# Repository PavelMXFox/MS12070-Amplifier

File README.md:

# Audio Amplifier System Design
##  Overview
This project is a professional-grade audio amplifier system featuring dual MA12070P Class-D amplifier chips in a 2×BTL configuration. The design includes a complete power supply section, digital signal processing (DSP) core, and control interfaces.

## Key Features
* Dual Channel Bi-Amplifier: 2×BTL configuration with MA12070P chips
* Digital Control: Integrated DSP for advanced audio processing
* Power Supply: 24V input with comprehensive protection circuitry
* Interfaces: I2C control, ADC inputs, and digital audio inputs
* Protection: Overvoltage, reverse polarity, and thermal monitoring

## Hardware Components
* Main Amplifiers: MA12070P Class-D amplifiers
* DSP Core: ADAU1452 audio processor
* Power Management: ADM1032 for rail monitoring
* Control MCU: STM32 microcontroller
* Audio Interfaces: PCM1808 for digital audio input

## Block Diagram Overview
The system consists of the following main sections:
* Power Section: 24V input with protection and distribution
* Amplifier Section: Dual MA12070P channels with complete driver circuitry
* DSP Section: Audio processing core with memory
* Control Section: MCU and interface circuits
* Audio Section: Input conditioning and output drivers

## Documentation
* Schematics: Detailed schematics for all sections
* PCB Layout: Professional-grade layout with proper grounding and power distribution
* Bill of Materials: Complete list of components
* Assembly Guide: Step-by-step assembly instructions
## License
This project is released under the TAPR Open Hardware License. All files are provided "as is" without warranty. For more details, see the LICENSE.TXT file.

## Contributions
* Original Power Supply Section: Based on Open Hardware DSP Platform (github.com:ohdsp/DSP-ADAU1452.git) under TAPR OHL
* Main Design: Developed by Pavel Dmitriev
* Modifications: See CHANGES.TXT for detailed list of changes

## How to Use
* Review the schematics and documentation
* Verify component compatibility
* Follow assembly guidelines
* Program the DSP and MCU
* Perform system calibration

## Known Issues
None reported at this time

## Contact
For questions or contributions, please contact:
GitHub: https://github.com/PavelMXFox

## Version History
* Initial release: November 2026
* Based on design principles from Open Hardware DSP Platform (github.com:ohdsp/DSP-ADAU1452.git)

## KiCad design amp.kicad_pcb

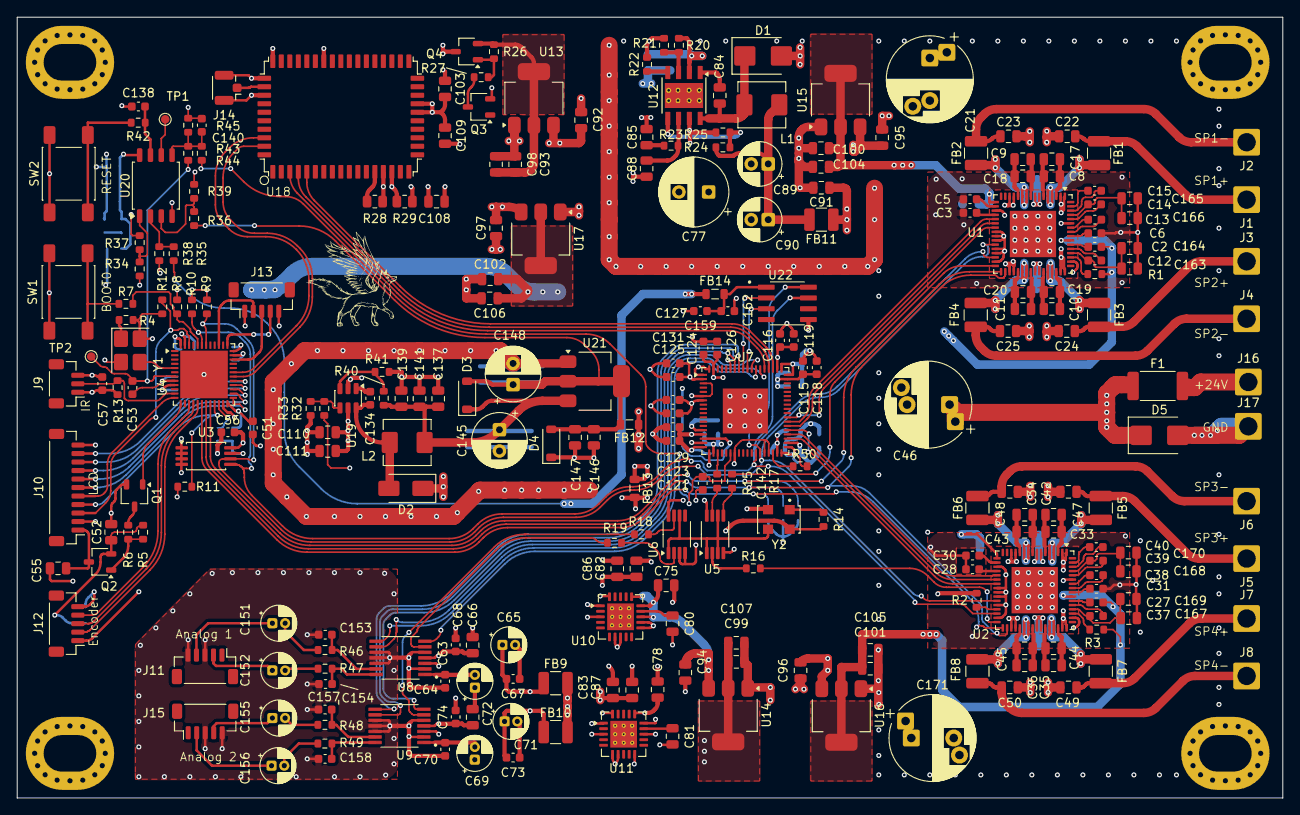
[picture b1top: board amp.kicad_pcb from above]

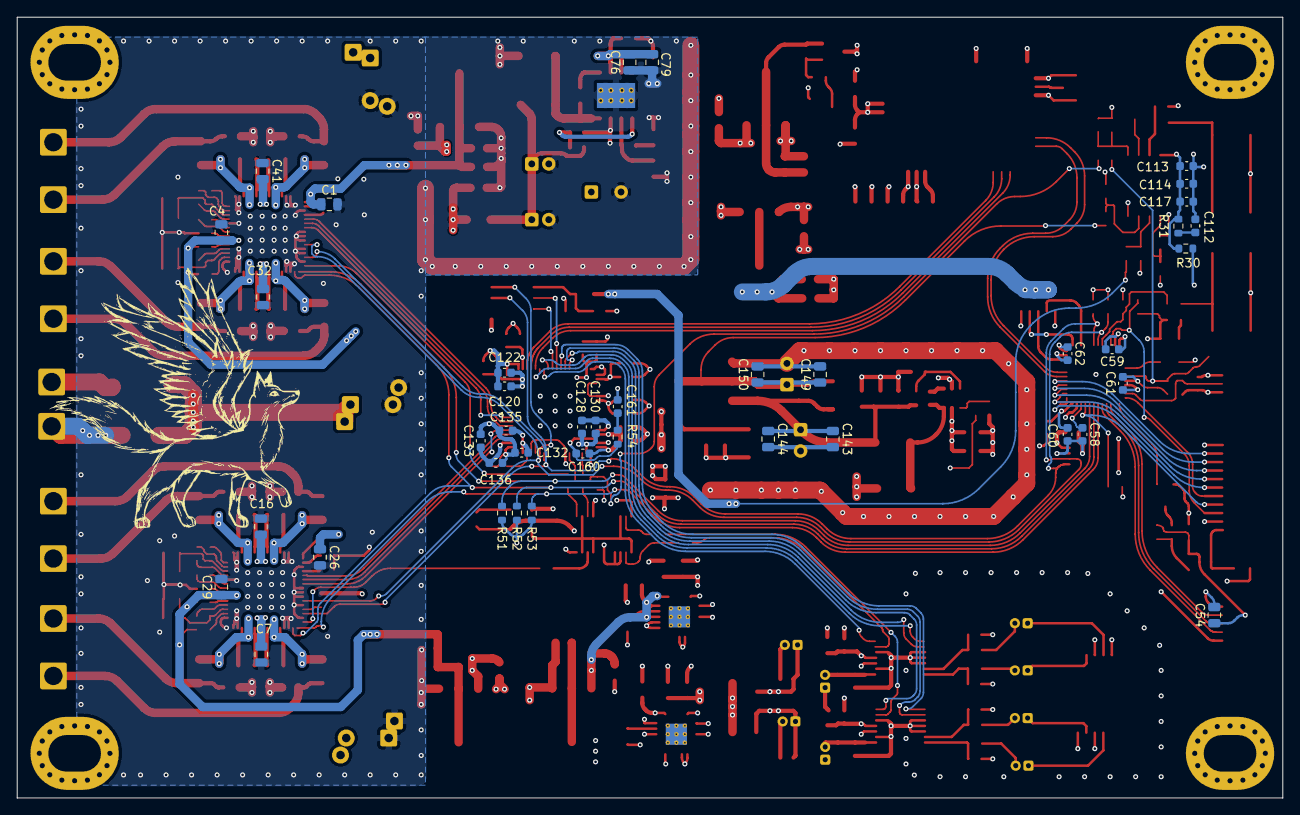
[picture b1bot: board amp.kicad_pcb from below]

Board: 4 copper layers, 148.8 x 91.8 mm, 296 parts (40 on the bottom side), 184 nets.

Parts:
C1, C4, C7, C16, C26, C29, C32, C41, C80, C81, C163, C165, C167, C168: 1uF; C_0805_2012Metric
C2, C3, C5, C6, C12, C13, C14, C27, C28, C30, C31, C37, C38, C39, C162: 1uF; C_0603_1608Metric
C8, C9, C10, C11, C17, C18, C19, C20, C33, C34, C35, C36, C42, C43, C44, C45, C52, C66, C72, C91, C92, C93, C94, C95, C96, C97, C99, C100, C101, C102, C108, C109: 10uF; C_0805_2012Metric
C15, C40, C64, C67, C68, C70, C73, C74, C159: 100nf; C_0603_1608Metric
C21, C46, C171: 470uF; CP_Radial_D10.0mm_P5.00mm_P7.50mm
C22, C23, C24, C25, C47, C48, C49, C50: 1nf; C_0805_2012Metric
C51, C53, C56, C59, C60, C61, C62, C114, C138, C140, C142: 100n; C_0603_1608Metric
C54, C55, C98, C103, C104, C105, C106, C107: 100nF; C_0805_2012Metric
C57, C118, C119, C122, C123, C126, C127, C130, C131, C135, C136: 100nF; C_0603_1608Metric
C58: 4.7uF; C_0603_1608Metric
C63, C65, C69, C71: 10uF; CP_Radial_D4.0mm_P1.50mm
C75, C78, C82, C83, C86, C87: 22uF; C_0805_2012Metric
C76, C79: 2.2uF; C_0805_2012Metric
C77: 100uF; CP_Radial_D8.0mm_P3.50mm
C84: 0.1uF; C_0805_2012Metric
C85: 6800pF; C_0805_2012Metric
C88: 39pF; C_0805_2012Metric
C89, C90: 47uF; CP_Radial_D5.0mm_P2.00mm
C110, C137, C139, C144, C147: 22u; C_0805_2012Metric
C111, C141, C143, C146, C149: 100n; C_0805_2012Metric
C112: 100p; C_0603_1608Metric
C113: 10u; C_0603_1608Metric
C115, C116, C120, C121, C124, C125, C128, C129, C132, C133: 10uF; C_0603_1608Metric
C117, C134: 10n; C_0603_1608Metric
C145, C148: 220u; CP_Radial_D6.3mm_P2.50mm
C150: 10u; C_0805_2012Metric
C151, C152, C155, C156: 2.2uF; CP_Radial_D4.0mm_P1.50mm
C153, C157: 1nF; C_0603_1608Metric
C154, C158: 1nf; C_0603_1608Metric
C160: 150pf; C_0603_1608Metric
C161: 5,6nF; C_0603_1608Metric
C164, C166, C169, C170: 100nf; C_0805_2012Metric
D1: B560C; D_SMB
D2: B240A; D_SMA
D3, D4: SS14L; D_SOD-123
D5: SMBJ24A; D_SMB
F1: 10A; Fuse_2512_6332Metric
FB1, FB2, FB3, FB4, FB5, FB6, FB7, FB8, FB11: FerriteBead; L_1210_3225Metric
FB9, FB10: L_1210_3225Metric
FB12, FB13, FB14: 600R@100MHz >1A; L_0805_2012Metric
J1, J5: SPK1P; SolderWire-1.5sqmm_1x01_D1.7mm_OD3mm
J2, J6: SPK1N; SolderWire-1.5sqmm_1x01_D1.7mm_OD3mm
J3, J7: SPK2P; SolderWire-1.5sqmm_1x01_D1.7mm_OD3mm
J4, J8: SPK2N; SolderWire-1.5sqmm_1x01_D1.7mm_OD3mm
J9: Conn_01x03; JST_SH_BM03B-SRSS-TB_1x03-1MP_P1.00mm_Vertical
J10: Conn_01x11; JST_SH_BM11B-SRSS-TB_1x11-1MP_P1.00mm_Vertical
J11, J15: Conn_01x05; JST_SH_BM05B-SRSS-TB_1x05-1MP_P1.00mm_Vertical
J12: Encoder; JST_SH_BM05B-SRSS-TB_1x05-1MP_P1.00mm_Vertical
J13: ST-Link; JST_SH_BM05B-SRSS-TB_1x05-1MP_P1.00mm_Vertical
J14: Conn_Coaxial; U.FL_Hirose_U.FL-R-SMT-1_Vertical
J16: 26V IN; SolderWire-1.5sqmm_1x01_D1.7mm_OD3mm
J17: GND; SolderWire-1.5sqmm_1x01_D1.7mm_OD3mm
L1, L2: 4.7uH; L_Sunlord_MWSA0518S
Q1, Q3: PDTC114ET; TSOT-23
Q2, Q4: IRLML2244; TSOT-23
R1, R2, R3: 1K; R_0603_1608Metric
R4, R8, R13, R50, R51, R52, R53: 10K; R_0603_1608Metric
R5, R26: 33K; R_0603_1608Metric
R6, R27: 330R; R_0603_1608Metric
R7, R46, R47, R48, R49: 100R; R_0603_1608Metric
R9, R10, R11, R12, R14: 4.7K; R_0603_1608Metric
R15, R16, R17, R18, R19: 33R; R_0603_1608Metric
R20: 523.0K; R_0603_1608Metric
R21: 84,5K; R_0603_1608Metric
R22: 45.3K; R_0603_1608Metric
R23: 13.0K; R_0603_1608Metric
R24: 66.5K; R_0603_1608Metric
R25: 10.2K; R_0603_1608Metric
R28: 1K; R_0805_2012Metric
R29: 100K; R_0805_2012Metric
R30: 1; R_0603_1608Metric
R31: 47; R_0603_1608Metric
R32: 16k; R_0603_1608Metric
R33: 10k; R_0603_1608Metric
R34: 0; R_0603_1608Metric
R35: 12k; R_0603_1608Metric
R36: 3k3; R_0603_1608Metric
R37: N/F; R_0603_1608Metric
R38: 3k; R_0603_1608Metric
R39: 3k6; R_0603_1608Metric
R40: 24k; R_0603_1608Metric
R41: 15k; R_0603_1608Metric
R42: 1k; R_0603_1608Metric
R43, R44: 100; R_0603_1608Metric
R45: 100k; R_0603_1608Metric
R54: 4,32K; R_0603_1608Metric
SW1: BOOT0; SW_Push_1P1T_NO_E-Switch_TL3301NxxxxxG
SW2: RESET; SW_Push_1P1T_NO_E-Switch_TL3301NxxxxxG
TP1, TP2: PIN; TestPoint_Pad_D1.0mm
U1, U2: MA12070P; QFN-64-1EP_9x9mm_P0.5mm_EP5.45x5.45mm
U3: 24LC256; TSSOP-8_4.4x3mm_P0.65mm
U4: STM32F411CEUx; QFN-48-1EP_7x7mm_P0.5mm_EP5.6x5.6mm
U5, U6: 74LVC3G34; Texas_S-PDSO-G8_3x3mm_P0.65mm
U7: ADAU1452; LFCSP-72-1EP_10x10mm_P0.5mm_EP5.3x5.3mm
U8, U9: PCM1808PWG4; SOP65P640X120-14N
U10, U11: TPS7A4701xRGW; Texas_RGW0020A_VQFN-20-1EP_5x5mm_P0.65mm_EP3.15x3.15mm_Ther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
U12: TPS54360DDA; TI_SO-PowerPAD-8_ThermalVias
U13, U14, U17: LDL1117-3.3; SOT-223-3_TabPin2
U15, U16: LDL1117-5; SOT-223-3_TabPin2
U18: QCC512X; QCC512X_Bluetooth_module
U19: ADP2301AUJZ; SOT-23-6
U20: ADM13307-5ARZ; SOIC-8_5.3x5.3mm_P1.27mm
U21: TLV1117LV12DCY; SOT-223-3_TabPin2
U22: ADM1032ARZ; SOIC127P600X175-8N
Y1: ASE-8MHz; Oscillator_SMD_Abracon_ASE-4Pin_3.2x2.5mm_HandSoldering
Y2: ASFLMB-12.288MHZ-LC-T; XTAL_ASFLMB-12.288MHZ-LC-T

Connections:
/Control plane/BOOT0: R7.2, R8.1, U4.44 (BOOT0)
/Control plane/CLK_8MHZ: U4.5 (PH0), Y1.3 (OUT)
/Control plane/SWCLK: J13.4, U4.37 (PA14)
/Control plane/SWDIO: J13.3, U4.34 (PA13)
/Control plane/SWO: J13.2, U4.39 (PB3)
/Power 2/2V1: C137.1, C139.1, C141.1, C143.1, C144.1, C145.1, D3.1 (K), L2.2, R40.2, U21.3 (VIN)
/Power/U18_FB: R24.2, R25.1, U12.5 (FB)
ADC0_BCK: U7.60 (BCLK_IN1), U8.8 (BCK)
ADC0_CLOCK: R19.2, U8.6 (SCKI)
ADC0_DOUT: U7.62 (SDATA_IN1), U8.9 (DOUT)
ADC0_LRCK: U7.61 (LRCLK_IN1/MP11), U8.7 (LRCK)
ADC1_BCK: U7.65 (BCLK_IN2), U9.8 (BCK)
ADC1_CLOCK: R18.2, U9.6 (SCKI)
ADC1_DOUT: U7.67 (SDATA_IN2), U9.9 (DOUT)
ADC1_LRCK: U7.66 (LRCLK_IN2/MP12), U9.7 (LRCK)
ADC_PWD_5: C83.1, C87.1, FB9.2, FB10.2, U11.1 (OUT), U11.3 (SENSE/FB), U11.20 (OUT)
ADC_PWR_3V3: C66.1, C68.1, C72.1, C74.1, C99.1, C107.1, U8.4 (VDD), U9.4 (VDD), U14.2 (VO)
BCLK_OUT0: U2.21 (SCLK), U7.40 (BCLK_OUT0)
BCLK_OUT1: U1.21 (SCLK), U7.43 (BCLK_OUT1)
BT_BCK: U7.57 (BCLK_IN0), U18.5 (BCK)
BT_DAT: U7.59 (SDATA_IN0), U18.3 (DATA)
BT_PWR_3V3: C103.1, C108.1, C109.1, Q4.3 (D), R28.1, R29.1, U18.14 (VCC_3V3), U18.23 (3V3_VPAD), U18.24 (3V3_VPAD)
BT_RLCK: U7.58 (LRCLK_IN0/MP10), U18.4 (LRCK)
BT_RX: U4.30 (PA9), U18.53 (RX)
BT_TX: U4.31 (PA10), U18.52 (TX)
BUS_6V: C52.1, C54.1, C75.1, C78.1, C91.1, C92.1, C94.1, C95.1, C96.1, C97.1, C110.2, C111.2, FB11.1, Q2.2 (S), R5.1, U10.13 (EN), U10.15 (IN), U10.16 (IN), U11.13 (EN), U11.15 (IN), U11.16 (IN), U13.3 (VI), U14.3 (VI), U15.3 (VI), U16.3 (VI), U17.3 (VI), U19.5 (IN)
CPU_PWR_3V3: C51.2, C56.2, C57.1, C59.1, C60.1, C61.1, C62.1, C102.1, C106.1, J9.1, J10.2, J12.1, J13.1, R4.1, R9.1, R10.1, R11.1, R12.1, R13.1, R30.2, R34.1, SW1.2, U3.8 (VCC), U4.9 (VDDA), U4.24 (VDD), U4.36 (VDD), U4.48 (VDD), U17.2 (VO), Y1.4 (Vdd)
CPU_RESET: C53.2, R44.1, TP2.1 (P1_1), U4.7 (NRST)
DSP_DVDD: C115.1, C118.1, C120.1, C122.1, C124.1, C126.1, C128.1, C130.1, C132.1, C135.1, FB12.1, U7.20 (DVDD), U7.35 (DVDD), U7.53 (DVDD), U7.71 (DVDD)
DSP_PLLFIT: C160.1, R54.1, U7.16 (PLLFILT)
DSP_PVDD: C116.1, C119.1, C121.1, C123.1, C125.1, C127.1, C129.1, C131.1, C133.1, C136.1, C160.2, C161.2, FB13.1, U7.2 (IOVDD), U7.7 (AVDD), U7.15 (PVDD), U7.18 (IOVDD), U7.38 (IOVDD), U7.56 (IOVDD)
DSP_PWR_1V2: C146.1, C147.1, C148.1, C149.1, C150.1, D3.2 (A), D4.2 (K), FB12.2, R36.1, U21.2 (VOUT)
DSP_PWR_3V3: C82.1, C86.1, FB13.2, FB14.1, R14.1, R32.2, R35.1, U5.8 (VCC), U6.8 (VCC), U10.1 (OUT), U10.3 (SENSE/FB), U10.20 (OUT), Y2.4 (VDD)
DSP_RESET: C142.1, R43.1, U7.24 (~RESET)
DSP_SELFBOOT: R50.1, U7.34 (SELFBOOT)
DSP_THD_M: U7.63 (THD_M), U22.3 (D-)
DSP_THD_P: U7.64 (THD_P), U22.2 (D+)
ENCODER_A: J12.3, U4.16 (PA6)
ENCODER_B: J12.2, U4.17 (PA7)
ENCODER_CLICK: J12.4, U4.15 (PA5)
GND: C1.2, C3.1, C4.2, C5.1, C6.1, C7.1, C16.1, C21.2, C22.2, C23.1, C24.2, C25.1, C26.2, C28.1, C29.2, C30.1, C31.1, C32.1, C41.1, C46.2, C47.2, C48.1, C49.2, C50.1, C51.1, C52.2, C53.1, C54.2, C55.2, C56.1, C57.2, C58.2, C59.2, C60.2, C61.2, C62.2, C63.1, C64.2, C65.2, C66.2, C67.1, C68.2, C69.1, C70.2, C71.2, C72.2, C73.1, C74.2, C75.2, C76.1, C77.2, C78.2, C79.1, C80.2, C81.2, C82.2, C83.2, C85.2, C86.2, C87.2, C88.2, C89.2, C90.2, C91.2, C92.2, C93.2, C94.2, C95.2, C96.2, C97.2, C98.2, C99.2, C100.2, C101.2, C102.2, C103.2, C104.2, C105.2, C106.2, C107.2, C108.2, C109.2, C110.1, C111.1, C112.2, C113.2, C114.2, C115.2, C116.2, C117.2, C118.2, C119.2, C120.2, C121.2, C122.2, C123.2, C124.2, C125.2, C126.2, C127.2, C128.2, C129.2, C130.2, C131.2, C132.2, C133.2, C135.2, C136.2, C137.2, C138.2, C139.2, C140.2, C141.2, C142.2, C143.2, C144.2, C145.2, C146.2, C147.2, C148.2, C149.2, C150.2, C153.1, C154.2, C157.1, C158.2, C159.2, C162.2, C163.2, C164.1, C165.2, C166.1, C167.2, C168.2, C169.1, C170.1, C171.1, D1.2 (A), D2.1 (A), D4.1 (A), D5.2 (A), J9.3, J10.11, J11.3, J11.5, J12.5, J13.5, J14.2 (Ext), J15.3, J15.5, J17.1 (Pin_1_1), Q1.2 (E), Q3.2 (E), R8.2, R21.2, R22.1, R25.2, R29.2, R33.1, R37.1, R38.1, R39.1, R41.1, R45.1, R50.2, R51.2, R52.2, R53.2, SW2.1, U1.1 (PVSS), U1.2 (PVSS), U1.13 (PVSS), U1.14 (PVSS), U1.19 (AVSS), U1.24 (SD1), U1.25 (AVSS), U1.26 (DVSS), U1.28 (AD0), U1.29 (AD1), U1.31 (CLKM/S), U1.35 (PVSS), U1.36 (PVSS), U1.47 (PVSS), U1.48 (PVSS), U1.50 (MSEL1), U1.59 (DVSS), U1.65, U2.1 (PVSS), U2.2 (PVSS), U2.13 (PVSS), U2.14 (PVSS), U2.19 (AVSS), U2.24 (SD1), U2.25 (AVSS), U2.26 (DVSS), U2.28 (AD0), U2.31 (CLKM/S), U2.35 (PVSS), U2.36 (PVSS), U2.47 (PVSS), U2.48 (PVSS), U2.50 (MSEL1), U2.59 (DVSS), U2.65, U3.1 (A0), U3.2 (A1), U3.3 (A2), U3.4 (GND), U3.7 (WP), U4.8 (VSSA), U4.23 (VSS), U4.35 (VSS), U4.47 (VSS), U4.49 (VSS), U5.4 (GND), U6.3, U6.4 (GND), U7.1 (DGND), U7.3 (VDRIVE), U7.6 (AGND), U7.14 (PGND), U7.17 (DGND), U7.19 (DGND), U7.25 (DGND), U7.32 (MOSI/ADDR1), U7.33 (SS/ADDR0), U7.36 (DGND), U7.37 (DGND), U7.54 (DGND), U7.55 (DGND), U7.72 (DGND), U7.73 (EP), U8.2 (AGND), U8.5 (DGND), U8.10 (MD0), U8.11 (MD1), U8.12 (FMT), U9.2 (AGND), U9.5 (DGND), U9.10 (MD0), U9.11 (MD1), U9.12 (FMT), U10.7 (GND), U10.8 (1.6V), U10.11 (0.2V), U10.12 (0.1V), U10.21 (EP), U11.6 (3.2V), U11.7 (GND), U11.10 (0.4V), U11.21 (EP), U12.7 (GND), U12.9 (GNDPAD), U13.1 (GND), U14.1 (GND), U15.1 (GND), U16.1 (GND), U17.1 (GND), U18.15 (GND), U18.38 (GND), U18.44 (GND), U18.45 (GND), U18.47 (GND), U19.2 (GND), U20.4 (GND), U21.1 (GND), U22.5 (GND), Y1.2 (GND), Y2.2 (GND)
I2C_SCL: R9.2, U1.27 (SCL), U2.27 (SCL), U3.6 (SCL), U4.42 (PB6), U7.31 (SCLK/SCL), U22.8 (SCLK)
I2C_SDA: R10.2, U1.30 (SDA), U2.30 (SDA), U3.5 (SDA), U4.43 (PB7), U7.30 (MISO/SDA), U22.7 (SDATA)
IR_RX: J9.2, R13.2, U4.11 (PA1)
LCD_BACKLIGHT: C55.1, J10.1, Q2.3 (D)
LCD_BL_PWM: Q1.1 (B), U4.13 (PA3)
LCD_I2C_SCL: J10.4, R11.2, U4.21 (PB10)
LCD_I2C_SDA: J10.3, R12.2, U4.46 (PB9)
LCD_SPI_CS: J10.6, U4.25 (PB12)
LCD_SPI_DC: J10.10, U4.29 (PA8)
LCD_SPI_MISO: J10.8, U4.27 (PB14)
LCD_SPI_MOSI: J10.9, U4.28 (PB15)
LCD_SPI_RST: J10.5, U4.12 (PA2)
LCD_SPI_SCK: J10.7, U4.26 (PB13)
LRCK_OUT0: U2.22 (WS), U7.39 (LRCLK_OUT0/MP4)
LRCK_OUT1: U1.22 (WS), U7.42 (LRCLK_OUT1/MP5)
unnamed: C85.1, R23.2
unnamed: C89.1, C90.1, FB11.2, L1.2, R24.1
unnamed: C112.1, R31.2
unnamed: C151.2, R46.1
unnamed: C152.2, R47.1
unnamed: C155.2, R48.1
unnamed: C156.2, R49.1
unnamed: C161.1, R54.2
unnamed: C84.2, D1.1 (K), L1.1, U12.8 (SW)
unnamed: C134.2, D2.2 (K), L2.1, U19.6 (SW)
unnamed: FB1.2, U1.4 (OUT0A), U1.5 (OUT0A)
unnamed: FB2.1, U1.10 (OUT0B), U1.11 (OUT0B)
unnamed: FB3.1, U1.44 (OUT1A), U1.45 (OUT1A)
unnamed: FB4.1, U1.38 (OUT1B), U1.39 (OUT1B)
unnamed: FB5.2, U2.4 (OUT0A), U2.5 (OUT0A)
unnamed: FB6.1, U2.10 (OUT0B), U2.11 (OUT0B)
unnamed: FB7.1, U2.44 (OUT1A), U2.45 (OUT1A)
unnamed: FB8.1, U2.38 (OUT1B), U2.39 (OUT1B)
unnamed: C22.1, FB1.1, J1.1 (Pin_1_1)
unnamed: C23.2, FB2.2, J2.1 (Pin_1_1)
unnamed: C24.1, FB3.2, J3.1 (Pin_1_1)
unnamed: C25.2, FB4.2, J4.1 (Pin_1_1)
unnamed: C47.1, FB5.1, J5.1 (Pin_1_1)
unnamed: C48.2, FB6.2, J6.1 (Pin_1_1)
unnamed: C49.1, FB7.2, J7.1 (Pin_1_1)
unnamed: C50.2, FB8.2, J8.1 (Pin_1_1)
unnamed: C152.1, J11.2
unnamed: C151.1, J11.4
unnamed: J14.1 (In), U18.46 (ANT)
unnamed: C156.1, J15.2
unnamed: C155.1, J15.4
unnamed: F1.2, J16.1 (Pin_1_1)
unnamed: Q1.3 (C), R6.2
unnamed: Q2.1 (G), R5.2, R6.1
unnamed: Q3.3 (C), R27.2
unnamed: Q4.1 (G), R26.2, R27.1
unnamed: C93.1, C98.1, Q4.2 (S), R26.1, U13.2 (VO)
unnamed: R7.1, SW1.1
unnamed: R15.2, U5.7
unnamed: R16.1, U5.2
unnamed: R17.1, U5.5
unnamed: R18.1, U6.7
unnamed: R19.1, U6.2
unnamed: R42.2, SW2.2
unnamed: TP1.1 (P1_1), U20.6 (RESET)
unnamed: C6.2, U1.56 (CDC)
unnamed: C8.2, C17.1, U1.3 (CF0AN)
unnamed: C8.1, C17.2, U1.6 (CF0AP)
unnamed: C9.2, C18.1, U1.12 (CF0BN)
unnamed: C9.1, C18.2, U1.9 (CF0BP)
unnamed: C10.2, C19.1, U1.46 (CF1AN)
unnamed: C10.1, C19.2, U1.43 (CF1AP)
unnamed: C11.2, C20.1, U1.37 (CF1BN)
unnamed: C11.1, C20.2, U1.40 (CF1BP)
unnamed: C13.2, U1.58 (CFDCN)
unnamed: C13.1, U1.57 (CFDCP)
unnamed: C15.2, U1.63 (CFGDN)
unnamed: C15.1, U1.62 (CFGDP)
unnamed: C14.2, C165.1, C166.2, U1.61 (CGD0N)
unnamed: C14.1, U1.60 (CGD0P)
unnamed: C12.2, C163.1, C164.2, U1.52 (CGD1N)
unnamed: C12.1, U1.53 (CGD1P)
unnamed: C5.2, U1.18 (CMSE)
unnamed: C3.2, U1.20 (CREF)
unnamed: R1.2, U1.51 (MSEL0)
unnamed: C2.2, U1.54 (VGDC)
unnamed: R2.2, U2.29 (AD1)
unnamed: C31.2, U2.56 (CDC)
unnamed: C33.2, C42.2, U2.3 (CF0AN)
unnamed: C33.1, C42.1, U2.6 (CF0AP)
unnamed: C34.2, C43.1, U2.12 (CF0BN)
unnamed: C34.1, C43.2, U2.9 (CF0BP)
unnamed: C35.2, C44.1, U2.46 (CF1AN)
unnamed: C35.1, C44.2, U2.43 (CF1AP)
unnamed: C36.2, C45.1, U2.37 (CF1BN)
unnamed: C36.1, C45.2, U2.40 (CF1BP)
unnamed: C38.2, U2.58 (CFDCN)
unnamed: C38.1, U2.57 (CFDCP)
unnamed: C40.2, U2.63 (CFGDN)
unnamed: C40.1, U2.62 (CFGDP)
unnamed: C39.2, C168.1, C170.2, U2.61 (CGD0N)
unnamed: C39.1, U2.60 (CGD0P)
unnamed: C37.2, C167.1, C169.2, U2.52 (CGD1N)
unnamed: C37.1, U2.53 (CGD1P)
unnamed: C30.2, U2.18 (CMSE)
unnamed: C28.2, U2.20 (CREF)
unnamed: R3.1, U2.51 (MSEL0)
unnamed: C27.2, U2.54 (VGDC)
unnamed: C58.1, U4.22 (VCAP1)
unnamed: R15.1, U7.21 (XTALIN/MCLK)
unnamed: C65.1, C67.2, FB9.1, U8.3 (VCC)
unnamed: C153.2, R46.2, U8.13 (VINL)
unnamed: C154.1, R47.2, U8.14 (VINR)
unnamed: C63.2, C64.1, U8.1 (VREF)
unnamed: C71.1, C73.2, FB10.1, U9.3 (VCC)
unnamed: C157.2, R48.2, U9.13 (VINL)
unnamed: C158.1, R49.2, U9.14 (VINR)
unnamed: C69.2, C70.1, U9.1 (VREF)
unnamed: C80.1, U10.14 (NR)
unnamed: C81.1, U11.14 (NR)
unnamed: C84.1, U12.1 (BOOT)
unnamed: C88.1, R23.1, U12.6 (COMP)
unnamed: R20.2, R21.1, U12.3 (EN)
unnamed: R22.2, U12.4 (RT/CLK)
unnamed: R28.2, U18.13 (MFB)
unnamed: C134.1, U19.1 (BS)
unnamed: R32.1, R33.2, U19.4 (EN)
unnamed: R40.1, R41.2, U19.3 (FB)
unnamed: R34.2, R37.2, U20.1 (SENSE1)
unnamed: R35.2, R38.2, U20.2 (SENSE2)
unnamed: R36.2, R39.2, U20.3 (SENSE3)
unnamed: C113.1, C114.1, C117.1, R30.1, R31.1, U20.8 (VDD)
unnamed: C138.1, R42.1, U20.7 (~MR)
unnamed: C140.1, R43.2, R44.2, R45.2, U20.5 (~RESET)
unnamed: C159.1, C162.1, FB14.2, U22.1 (VDD)
unnamed: R4.2, Y1.1 (EN)
unnamed: U5.1, U5.3, U5.6, U6.1, U6.6, Y2.3 (OUTPUT)
unnamed: R14.2, Y2.1 (STANDBY)
PA1_CLOCK: R17.2, U1.32 (CLK)
PA1_ENABLE: R51.1, U1.33 (~ENABLE), U4.20 (PB2)
PA1_PWR_5: C1.1, C2.1, C4.1, C100.1, C104.1, R1.1, U1.17 (AVDD), U1.55 (DVDD), U15.2 (VO)
PA2_CLOCK: R16.2, U2.32 (CLK)
PA2_ENABLE: R53.1, U2.33 (~ENABLE), U4.18 (PB0)
PA2_PWR_5: C26.1, C27.1, C29.1, C101.1, C105.1, R2.1, R3.2, U2.17 (AVDD), U2.55 (DVDD), U16.2 (VO)
PA_MUTE: R52.1, U1.34 (~MUTE), U2.34 (~MUTE), U4.19 (PB1)
PVCC: C7.2, C16.2, C21.1, C32.2, C41.2, C46.1, C76.2, C77.1, C79.2, C171.2, D5.1 (K), F1.1, R20.1, U1.7 (PVDD), U1.8 (PVDD), U1.41 (PVDD), U1.42 (PVDD), U2.7 (PVDD), U2.8 (PVDD), U2.41 (PVDD), U2.42 (PVDD), U12.2 (VIN)
SDATA_OUT0: U2.23 (SD0), U7.41 (SDATA_OUT0)
SDATA_OUT1: U1.23 (SD0), U7.44 (SDATA_OUT1)
